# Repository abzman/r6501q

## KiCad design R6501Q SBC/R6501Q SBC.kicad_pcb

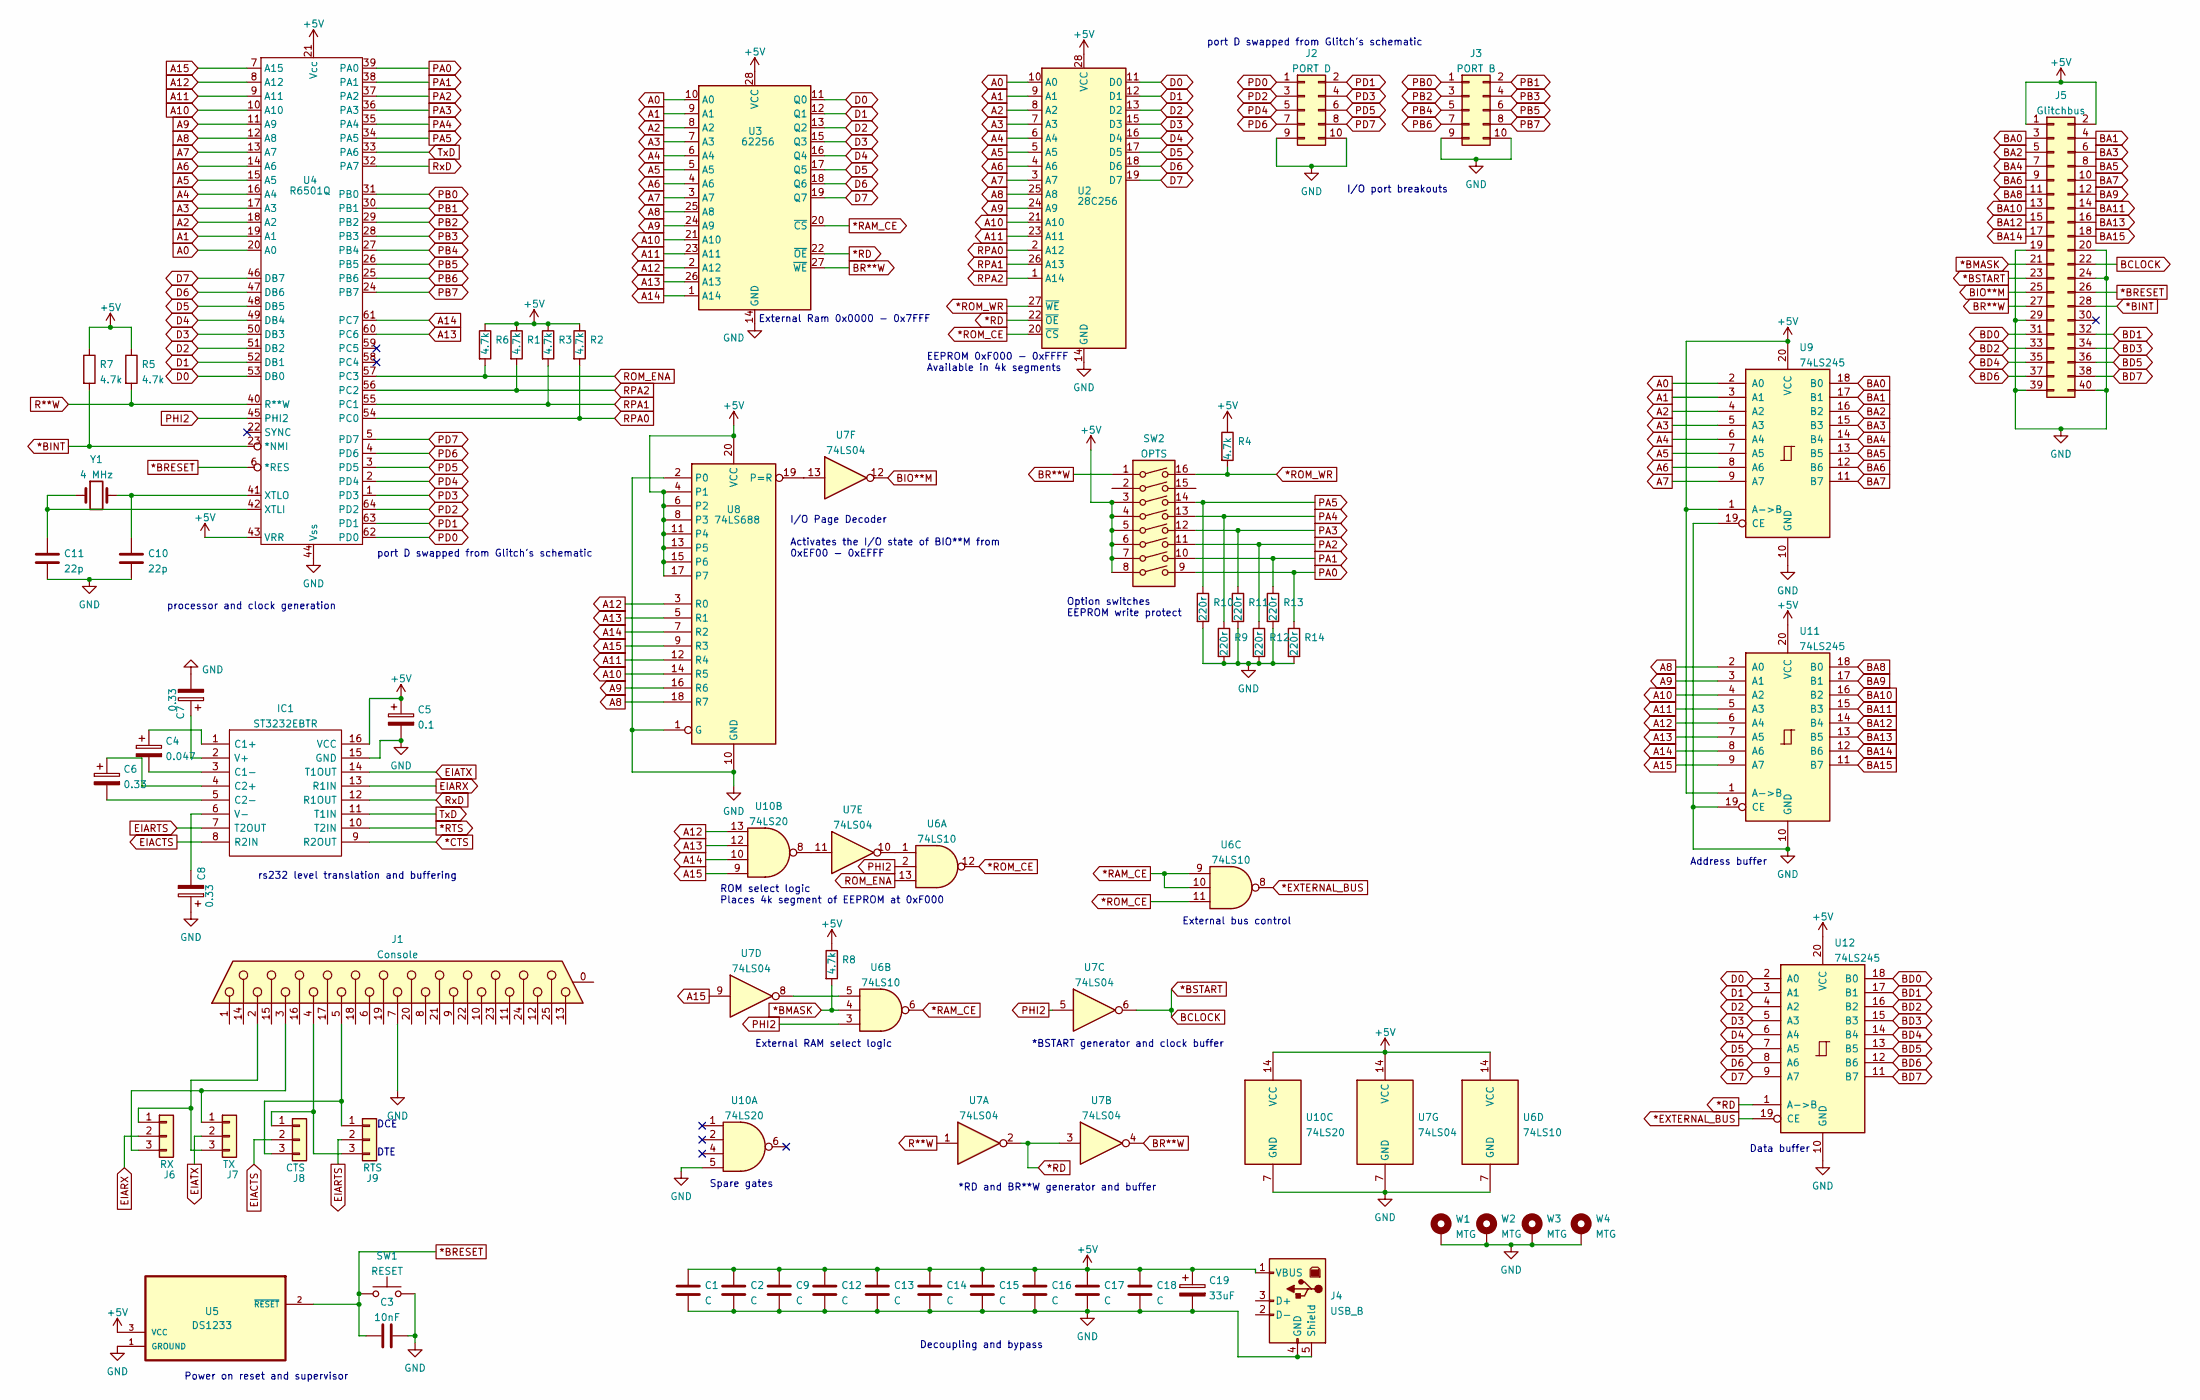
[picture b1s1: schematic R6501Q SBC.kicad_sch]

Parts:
C1, C2, C9, C12, C13, C14, C15, C16, C17, C18: C; C_0603_1608Metric
C3: 10nF; C_0603_1608Metric
C4: 0.047; C_0603_1608Metric
C5: 0.1; C_0603_1608Metric
C6, C7, C8: 0.33; C_0603_1608Metric
C10, C11: 22p; C_0603_1608Metric
C19: 33uF; CP_Radial_D6.3mm_P2.50mm
IC1: ST3232EBTR; SOP65P640X120-16N; Mouser Part Number 511-ST3232EB
J1: Console; amphenol db25
J2: PORT D; PinHeader_2x05_P2.54mm_Vertical
J3: PORT B; PinHeader_2x05_P2.54mm_Vertical
J4: USB_B; USB_B_OST_USB-B1HSxx_Horizontal
J5: Glitchbus; PinHeader_2x20_P2.54mm_Vertical
J6: RX; PinHeader_1x03_P2.54mm_Vertical
J7: TX; PinHeader_1x03_P2.54mm_Vertical
J8: CTS; PinHeader_1x03_P2.54mm_Vertical
J9: RTS; PinHeader_1x03_P2.54mm_Vertical
R1, R2, R3, R4, R5, R6, R7, R8: 4.7k; R_0603_1608Metric
R9, R10, R11, R12, R13, R14: 220r; R_0603_1608Metric
SW1: RESET; SW_Tactile_SPST_Angled_PTS645Vx39-2LFS
SW2: OPTS; SW_DIP_SPSTx08_Slide_9.78x22.5mm_W7.62mm_P2.54mm
U2: 28C256; DIP-28_W15.24mm
U3: 62256; DIP-28_W15.24mm
U4: R6501Q; QUIP64
U5: DS1233; TO92127P495H695-3
U6: 74LS10; DIP-14_W7.62mm
U7: 74LS04; DIP-14_W7.62mm
U8: 74LS688; DIP-20_W7.62mm
U9, U11, U12: 74LS245; DIP-20_W7.62mm
U10: 74LS20; DIP-14_W7.62mm
W1, W2, W3, W4: MTG; MountingHole_3.2mm_M3_DIN965_Pad
Y1: 4 MHz; Crystal_HC49-U_Vertical

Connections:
*BINT: J5.28, R7.2, U4.23 (*NMI)
*BMASK: J5.21, R8.2, U6.4
*BRESET: C3.2, J5.26, SW1.2, U4.6 (*RES), U5.2 (~RESET)
*BSTART: J5.22, J5.23, U7.6
*CTS: IC1.9 (R2OUT)
*EXTERNAL_BUS: U6.8, U12.19 (CE)
*RAM_CE: U3.20 (~CS), U6.6, U6.9, U6.10
*RD: U2.22 (~OE), U3.22 (~OE), U7.2, U7.3, U12.1 (A->B)
*ROM_CE: U2.20 (~CS), U6.11, U6.12
*ROM_WR: R4.2, SW2.16, U2.27 (~WE)
*RTS: IC1.10 (T2IN)
+5V: C1.1, C2.1, C5.1, C9.1, C12.1, C13.1, C14.1, C15.1, C16.1, C17.1, C18.1, C19.1, IC1.16 (VCC), J4.1 (VBUS), J5.1, J5.2, R1.1, R2.1, R3.1, R4.1, R5.1, R6.1, R7.1, R8.1, SW2.3, SW2.4, SW2.5, SW2.6, SW2.7, SW2.8, U2.28 (VCC), U3.28 (VCC), U4.21 (Vcc), U4.43 (VRR), U5.3 (VCC), U6.14 (VCC), U7.14 (VCC), U8.4 (P1), U8.6 (P2), U8.8 (P3), U8.11 (P4), U8.13 (P5), U8.15 (P6), U8.17 (P7), U8.20 (VCC), U9.1 (A->B), U9.20 (VCC), U10.14 (VCC), U11.1 (A->B), U11.20 (VCC), U12.20 (VCC)
A0: U2.10 (A0), U3.10 (A0), U4.20 (A0), U9.2 (A0)
A1: U2.9 (A1), U3.9 (A1), U4.19 (A1), U9.3 (A1)
A2: U2.8 (A2), U3.8 (A2), U4.18 (A2), U9.4 (A2)
A3: U2.7 (A3), U3.7 (A3), U4.17 (A3), U9.5 (A3)
A4: U2.6 (A4), U3.6 (A4), U4.16 (A4), U9.6 (A4)
A5: U2.5 (A5), U3.5 (A5), U4.15 (A5), U9.7 (A5)
A6: U2.4 (A6), U3.4 (A6), U4.14 (A6), U9.8 (A6)
A7: U2.3 (A7), U3.3 (A7), U4.13 (A7), U9.9 (A7)
A8: U2.25 (A8), U3.25 (A8), U4.12 (A8), U8.18 (R7), U11.2 (A0)
A9: U2.24 (A9), U3.24 (A9), U4.11 (A9), U8.16 (R6), U11.3 (A1)
A10: U2.21 (A10), U3.21 (A10), U4.10 (A10), U8.14 (R5), U11.4 (A2)
A11: U2.23 (A11), U3.23 (A11), U4.9 (A11), U8.12 (R4), U11.5 (A3)
A12: U3.2 (A12), U4.8 (A12), U8.3 (R0), U10.13, U11.6 (A4)
A13: U3.26 (A13), U4.60 (PC6), U8.5 (R1), U10.12, U11.7 (A5)
A14: U3.1 (A14), U4.61 (PC7), U8.7 (R2), U10.10, U11.8 (A6)
A15: U4.7 (A15), U7.9, U8.9 (R3), U10.9, U11.9 (A7)
BA0: J5.3, U9.18 (B0)
BA1: J5.4, U9.17 (B1)
BA2: J5.5, U9.16 (B2)
BA3: J5.6, U9.15 (B3)
BA4: J5.7, U9.14 (B4)
BA5: J5.8, U9.13 (B5)
BA6: J5.9, U9.12 (B6)
BA7: J5.10, U9.11 (B7)
BA8: J5.11, U11.18 (B0)
BA9: J5.12, U11.17 (B1)
BA10: J5.13, U11.16 (B2)
BA11: J5.14, U11.15 (B3)
BA12: J5.15, U11.14 (B4)
BA13: J5.16, U11.13 (B5)
BA14: J5.17, U11.12 (B6)
BA15: J5.18, U11.11 (B7)
BD0: J5.31, U12.18 (B0)
BD1: J5.32, U12.17 (B1)
BD2: J5.33, U12.16 (B2)
BD3: J5.34, U12.15 (B3)
BD4: J5.35, U12.14 (B4)
BD5: J5.36, U12.13 (B5)
BD6: J5.37, U12.12 (B6)
BD7: J5.38, U12.11 (B7)
BIO**M: J5.25, U7.12
BR**W: J5.27, SW2.1, U3.27 (~WE), U7.4
D0: U2.11 (D0), U3.11 (Q0), U4.53 (DB0), U12.2 (A0)
D1: U2.12 (D1), U3.12 (Q1), U4.52 (DB1), U12.3 (A1)
D2: U2.13 (D2), U3.13 (Q2), U4.51 (DB2), U12.4 (A2)
D3: U2.15 (D3), U3.15 (Q3), U4.50 (DB3), U12.5 (A3)
D4: U2.16 (D4), U3.16 (Q4), U4.49 (DB4), U12.6 (A4)
D5: U2.17 (D5), U3.17 (Q5), U4.48 (DB5), U12.7 (A5)
D6: U2.18 (D6), U3.18 (Q6), U4.47 (DB6), U12.8 (A6)
D7: U2.19 (D7), U3.19 (Q7), U4.46 (DB7), U12.9 (A7)
EIACTS: IC1.8 (R2IN), J8.2
EIARTS: IC1.7 (T2OUT), J9.2
EIARX: IC1.13 (R1IN), J6.2
EIATX: IC1.14 (T1OUT), J7.2
GND: C1.2, C2.2, C3.1, C5.2, C7.2, C8.1, C9.2, C10.2, C11.2, C12.2, C13.2, C14.2, C15.2, C16.2, C17.2, C18.2, C19.2, IC1.15 (GND), J1.7, J1.MH1, J1.MH2, J2.9, J2.10, J3.9, J3.10, J4.4 (GND), J4.5 (Shield), J5.19, J5.20, J5.24, J5.29, J5.39, J5.40, R9.2, R10.2, R11.2, R12.2, R13.2, R14.2, SW1.1, U2.14 (GND), U3.14 (GND), U4.44 (Vss), U5.1 (GROUND), U6.7 (GND), U7.7 (GND), U8.1 (G), U8.2 (P0), U8.10 (GND), U9.10 (GND), U9.19 (CE), U10.5, U10.7 (GND), U11.10 (GND), U11.19 (CE), U12.10 (GND), W1.1, W2.1, W3.1, W4.1
unnamed: C4.1, IC1.1 (C1+)
unnamed: C4.2, IC1.3 (C1-)
unnamed: C6.1, IC1.4 (C2+)
unnamed: C6.2, IC1.5 (C2-)
unnamed: C7.1, IC1.2 (V+)
unnamed: C8.2, IC1.6 (V-)
unnamed: C10.1, U4.41 (XTLO), Y1.2
unnamed: C11.1, U4.42 (XTLI), Y1.1
unnamed: J1.2, J6.1, J7.3
unnamed: J1.3, J6.3, J7.1
unnamed: J1.4, J8.1, J9.3
unnamed: J1.5, J8.3, J9.1
unnamed: U6.1, U7.10
unnamed: U6.5, U7.8
unnamed: U7.13, U8.19 (P=R)
unnamed: U7.11, U10.8
PA0: R14.1, SW2.9, U4.39 (PA0)
PA1: R13.1, SW2.10, U4.38 (PA1)
PA2: R12.1, SW2.11, U4.37 (PA2)
PA3: R11.1, SW2.12, U4.36 (PA3)
PA4: R9.1, SW2.13, U4.35 (PA4)
PA5: R10.1, SW2.14, U4.34 (PA5)
PB0: J3.1, U4.31 (PB0)
PB1: J3.2, U4.30 (PB1)
PB2: J3.3, U4.29 (PB2)
PB3: J3.4, U4.28 (PB3)
PB4: J3.5, U4.27 (PB4)
PB5: J3.6, U4.26 (PB5)
PB6: J3.7, U4.25 (PB6)
PB7: J3.8, U4.24 (PB7)
PD0: J2.1, U4.62 (PD0)
PD1: J2.2, U4.63 (PD1)
PD2: J2.3, U4.64 (PD2)
PD3: J2.4, U4.1 (PD3)
PD4: J2.5, U4.2 (PD4)
PD5: J2.6, U4.3 (PD5)
PD6: J2.7, U4.4 (PD6)
PD7: J2.8, U4.5 (PD7)
PHI2: U4.45 (PHI2), U6.2, U6.3, U7.5
R**W: R5.2, U4.40 (R**W), U7.1
ROM_ENA: R6.2, U4.57 (PC3), U6.13
RPA0: R2.2, U2.2 (A12), U4.54 (PC0)
RPA1: R3.2, U2.26 (A13), U4.55 (PC1)
RPA2: R1.2, U2.1 (A14), U4.56 (PC2)
RxD: IC1.12 (R1OUT), U4.32 (PA7)
TxD: IC1.11 (T1IN), U4.33 (PA6)

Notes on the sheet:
port D swapped from Glitch's schematic
External RAM select logic
Spare gates
processor and clock generation
DCE
Power on reset and supervisor
DTE
Decoupling and bypass
Data buffer
External Ram 0x0000 - 0x7FFF
Address buffer
*BSTART generator and clock buffer
External bus control
EEPROM 0xF000 - 0xFFFF Available in 4k segments
I/O port breakouts
Option switches EEPROM write protect
rs232 level translation and buffering
*RD and BR**W generator and buffer
I/O Page Decoder Activates the I/O state of BIO**M from 0xEF00 - 0xEFFF
ROM select logic Places 4k segment of EEPROM at 0xF000

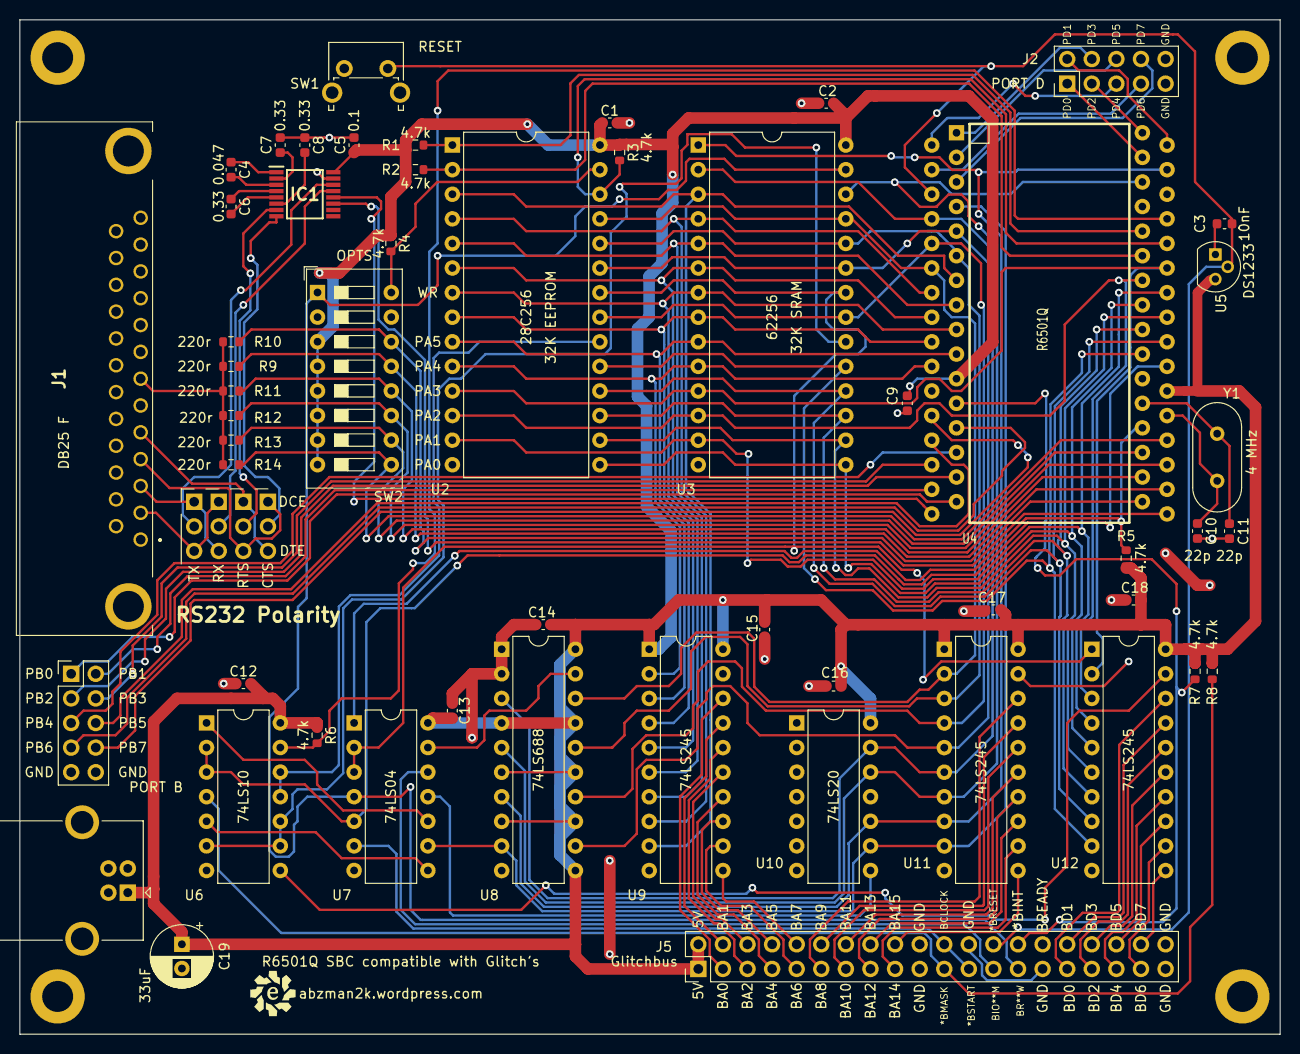
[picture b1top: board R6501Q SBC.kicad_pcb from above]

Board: 2 copper layers, 130.2 x 104.8 mm, 61 parts (0 on the bottom side), 111 nets.

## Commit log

2022-07-23 first board
2024-02-10 stuff
